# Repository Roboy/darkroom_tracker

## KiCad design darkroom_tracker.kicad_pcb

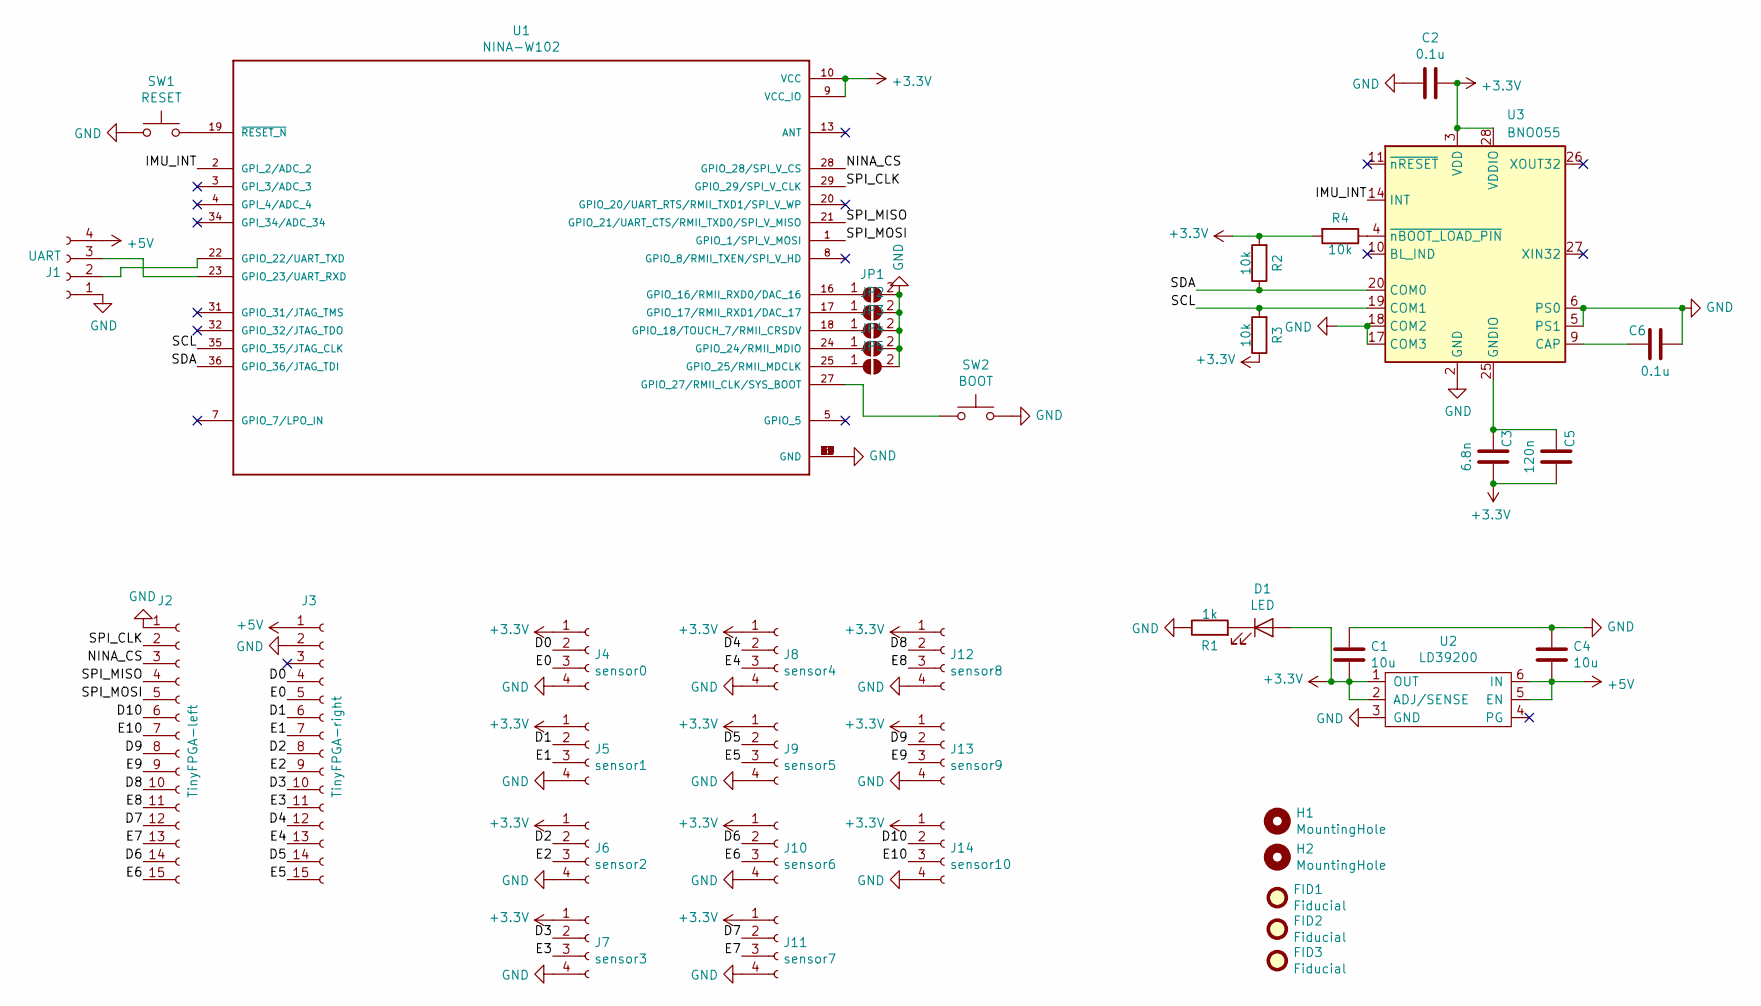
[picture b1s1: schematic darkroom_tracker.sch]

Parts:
C1, C4: 10u; C_0402_1005Metric
C2, C6: 0.1u; C_0402_1005Metric
C3: 6.8n; C_0402_1005Metric
C5: 120n; C_0402_1005Metric
D1: LED; LED_0402_1005Metric
FID1: Fiducial; R1_ear_silk_5.5mm
FID2: Fiducial; R1_eyes_mask_5.5mm
FID3: Fiducial; R1_face_mask_5.5mm
H1, H2: MountingHole; MountingHole_2.2mm_M2
J1: UART; TE-Connectivity_Micro-Match_connector_02x02_Pitch_1.27mm
J2: TinyFPGA-left; PinSocket_1x15_P2.54mm_Vertical
J3: TinyFPGA-right; PinSocket_1x15_P2.54mm_Vertical
J4: sensor0; TE-Connectivity_Micro-Match_connector_02x02_Pitch_1.27mm
J5: sensor1; TE-Connectivity_Micro-Match_connector_02x02_Pitch_1.27mm
J6: sensor2; TE-Connectivity_Micro-Match_connector_02x02_Pitch_1.27mm
J7: sensor3; TE-Connectivity_Micro-Match_connector_02x02_Pitch_1.27mm
J8: sensor4; TE-Connectivity_Micro-Match_connector_02x02_Pitch_1.27mm
J9: sensor5; TE-Connectivity_Micro-Match_connector_02x02_Pitch_1.27mm
J10: sensor6; TE-Connectivity_Micro-Match_connector_02x02_Pitch_1.27mm
J11: sensor7; TE-Connectivity_Micro-Match_connector_02x02_Pitch_1.27mm
J12: sensor8; TE-Connectivity_Micro-Match_connector_02x02_Pitch_1.27mm
J13: sensor9; TE-Connectivity_Micro-Match_connector_02x02_Pitch_1.27mm
J14: sensor10; TE-Connectivity_Micro-Match_connector_02x02_Pitch_1.27mm
JP1, JP2, JP3, JP4, JP5: SolderJumper_2_Open; SolderJumper-2_P1.3mm_Open_RoundedPad1.0x1.5mm
R1: 1k; R_0402_1005Metric
R2, R3, R4: 10k; R_0402_1005Metric
SW1: RESET; SW_SPST_KXT3
SW2: BOOT; SW_SPST_KXT3
U1: NINA-W102; XCVR_NINA-W102
U2: LD39200; DFN-6-1EP_3x3mm_P1mm_EP1.5x2.4mm
U3: BNO055; LGA-28_5.2x3.8mm_P0.5mm

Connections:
+3V3: C1.2, C2.1, C3.1, C5.1, D1.2 (A), J4.1, J5.1, J6.1, J7.1, J8.1, J9.1, J10.1, J11.1, J12.1, J13.1, J14.1, R2.2, R3.1, R4.2, U1.9 (VCC_IO), U1.10 (VCC), U2.1 (OUT), U2.2 (ADJ/SENSE), U3.3 (VDD), U3.28 (VDDIO)
+5V: C4.2, J1.4, J3.1, U2.5 (EN), U2.6 (IN)
/D0: J3.4, J4.2
/D1: J3.6, J5.2
/D2: J3.8, J6.2
/D3: J3.10, J7.2
/D4: J3.12, J8.2
/D5: J3.14, J9.2
/D6: J2.14, J10.2
/D7: J2.12, J11.2
/D8: J2.10, J12.2
/D9: J2.8, J13.2
/D10: J2.6, J14.2
/E0: J3.5, J4.3
/E1: J3.7, J5.3
/E2: J3.9, J6.3
/E3: J3.11, J7.3
/E4: J3.13, J8.3
/E5: J3.15, J9.3
/E6: J2.15, J10.3
/E7: J2.13, J11.3
/E8: J2.11, J12.3
/E9: J2.9, J13.3
/E10: J2.7, J14.3
/IMU_INT: U1.2 (GPI_2/ADC_2), U3.14 (INT)
/NINA_CS: J2.3, U1.28 (GPIO_28/SPI_V_CS)
/SCL: R3.2, U1.35 (GPIO_35/JTAG_CLK), U3.19 (COM1)
/SDA: R2.1, U1.36 (GPIO_36/JTAG_TDI), U3.20 (COM0)
/SPI_CLK: J2.2, U1.29 (GPIO_29/SPI_V_CLK)
/SPI_MISO: J2.4, U1.21 (GPIO_21/UART_CTS/RMII_TXD0/SPI_V_MISO)
/SPI_MOSI: J2.5, U1.1 (GPIO_1/SPI_V_MOSI)
GND: C1.1, C2.2, C4.1, C6.1, J1.1, J2.1, J3.2, J4.4, J5.4, J6.4, J7.4, J8.4, J9.4, J10.4, J11.4, J12.4, J13.4, J14.4, JP1.2 (B), JP2.2 (B), JP3.2 (B), JP4.2 (B), JP5.2 (B), R1.1, SW1.1, SW2.2, U1.6 (GND), U1.12 (GND), U1.14 (GND), U1.26 (GND), U1.30 (GND), U1.37 (GND), U1.38 (GND), U1.39 (GND), U1.40 (GND), U1.41 (GND), U1.42 (GND), U1.43 (GND), U1.44 (GND), U1.45 (GND), U1.46 (GND), U1.47 (GND), U1.48 (GND), U2.3 (GND), U3.2 (GND), U3.5 (PS1), U3.6 (PS0), U3.17 (COM3), U3.18 (COM2)
unnamed: C3.2, C5.2, U3.15 (GNDIO), U3.16 (GNDIO), U3.25 (GNDIO)
unnamed: C6.2, U3.9 (CAP)
unnamed: D1.1 (K), R1.2
unnamed: J1.2, U1.22 (GPIO_22/UART_TXD)
unnamed: J1.3, U1.23 (GPIO_23/UART_RXD)
unnamed: JP1.1 (A), U1.16 (GPIO_16/RMII_RXD0/DAC_16)
unnamed: JP2.1 (A), U1.17 (GPIO_17/RMII_RXD1/DAC_17)
unnamed: JP3.1 (A), U1.18 (GPIO_18/TOUCH_7/RMII_CRSDV)
unnamed: JP4.1 (A), U1.24 (GPIO_24/RMII_MDIO)
unnamed: JP5.1 (A), U1.25 (GPIO_25/RMII_MDCLK)
unnamed: R4.1, U3.4 (~nBOOT_LOAD_PIN)
unnamed: SW1.2, U1.19 (~RESET_N~)
unnamed: SW2.1, U1.27 (GPIO_27/RMII_CLK/SYS_BOOT)

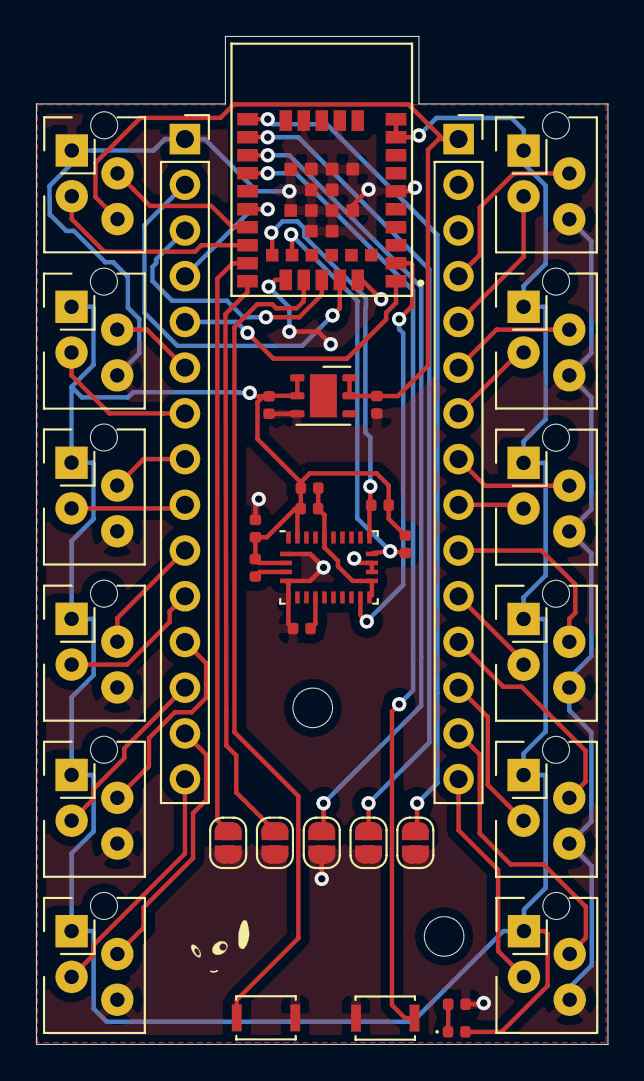
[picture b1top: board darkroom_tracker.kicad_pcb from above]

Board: 2 copper layers, 31.8 x 56.0 mm, 40 parts (0 on the bottom side), 45 nets.

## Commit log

2019-11-19 initial
